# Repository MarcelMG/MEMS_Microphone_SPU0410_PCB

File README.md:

# MEMS_Microphone_SPU0410_PCB
A PCB design for prototyping the Knowles SPU0410 MEMS Ultrasonic Microphone

This is a PCB designed for the Knowles SPU0410LR5H MEMS Microphone [(datasheet link)](https://www.knowles.com/docs/default-source/model-downloads/spu0410lr5h-qb-revh.pdf).
The SPU0410 microphone has the characteristic of beeing sensitive well beyond the audible audio spectrum in the ultrasonic (up to 80kHz and probably above).
Sadly, the microphone is in really tiny package with solder pads beneath the package, which makes it highly unsuited for hobbyists or prototyping.
The PCB uses a special footprint that still allows to solder the microphone by hand, the idea for this comes from hackaday.io user [Alan Green](https://hackaday.io/alang), you can read more about it [here](https://hackaday.io/project/165081-blue-board-01/details). I recorded the hand soldering process, you can watch a video of it [here](https://vimeo.com/430343841).
The input port of the microphone is on the backside of the PCB.
The design additionally includes a dual opamp that provides a buffered virtual ground (Vcc/2) as well as +20dB of flat gain. The recommended power supply range is between 1.8V and 3.6V.

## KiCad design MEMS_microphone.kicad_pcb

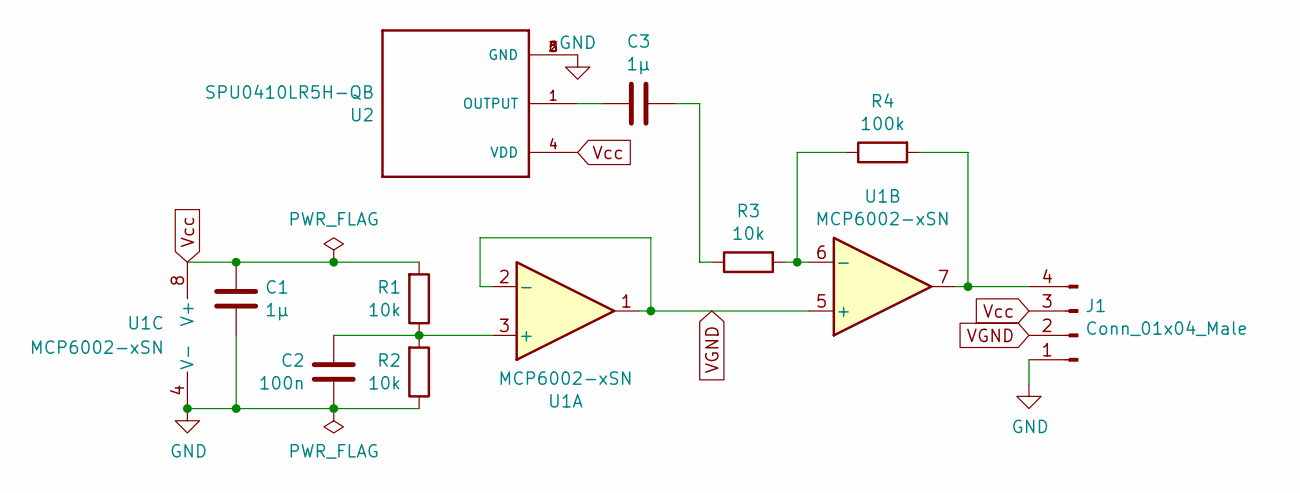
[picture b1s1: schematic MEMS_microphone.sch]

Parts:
C1, C3: 1µ; C_0805_2012Metric_Pad1.15x1.40mm_HandSolder
C2: 100n; C_0805_2012Metric_Pad1.15x1.40mm_HandSolder
J1: Conn_01x04_Male; PinHeader_1x04_P2.54mm_Horizontal
R1, R2, R3: 10k; R_0805_2012Metric_Pad1.15x1.40mm_HandSolder
R4: 100k; R_0805_2012Metric_Pad1.15x1.40mm_HandSolder
U1: MCP6002-xSN; SOIC-8_elongated_pads_MARCEL
U2: SPU0410LR5H-QB; SPU0410LR5H-QB_HANDSOLDER

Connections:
GND: C1.2, C2.1, J1.1, R2.1, U1.4 (V-), U2.2 (GND), U2.3 (GND), U2.5 (GND), U2.6 (GND)
unnamed: C2.2, R1.1, R2.2, U1.3 (+)
unnamed: C3.1, U2.1 (OUTPUT)
unnamed: C3.2, R3.1
unnamed: J1.4, R4.2, U1.7
unnamed: R3.2, R4.1, U1.6 (-)
VGND: J1.2, U1.1, U1.2 (-), U1.5 (+)
Vcc: C1.1, J1.3, R1.2, U1.8 (V+), U2.4 (VDD)

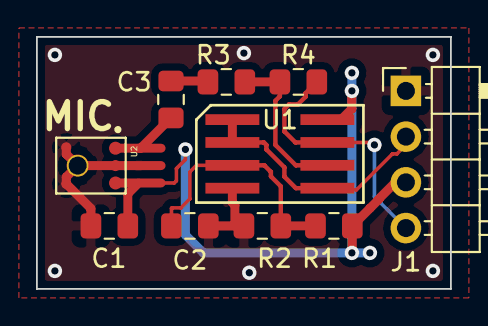
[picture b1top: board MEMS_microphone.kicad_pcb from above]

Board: 2 copper layers, 23.0 x 14.0 mm, 10 parts (0 on the bottom side), 8 nets.
